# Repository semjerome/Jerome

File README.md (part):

---
csl: apa.csl
bibliography: GNoiseCitations.bib
title: Telematics
author: "Jerome Aganon, Jabneel Cruz, Jaewoong Kang, Achille Mattapullut"
---

\vfill   March 28th, 2017

\linespread{2} \selectfont

Project Build Website: http://Semjerome.github.io

Project Official website: http://www.autaccreport.com/wordpresstest/

\pagebreak

Declaration of Joint Authorship
===============================

We, the Galaxy Noise, confirm that this work submitted for assessment is our own
and is expressed in our own words. Any uses that was used in this documents that
came from any other authors were acknowledged where their works were used. A
list of references are included in this document and the work breakdown can be
find on Overall Description Section 2.3.

Galaxy Noise: Jerome Aganon, Jabneel Cruz, Jaewhoong Kang, Achille Mattapullut

Date: February 6, 2017

\pagebreak

Proposal
========

Submission January 17, 2017

Prepared by Galaxy Noise (Jerome, Jabneel, Jaewoong)

Computer Engineering Technology Student

https://semjerome.github.io

**Executive Summary**

As students in the Computer Engineering Technology program, we will be
integrating the knowledge and skills we have learned from our program into this
Internet of Things themed capstone project. This proposal requests the approval
to build the hardware portion that will connect to a database as well as to a
mobile device application. The internet connected hardware will include a custom
PCB with sensors and /or actuators for detecting car collision and save the
captured image/video in a black box The database will store the timestamp and
the folder location of the video that were saved in the blackbox. The mobile
device functionality will include notifying the car owner of an accident
happening and if possible, an image or video capture of the accident and will be
further detailed in the mobile application proposal. We will be collaborating
with the following company/department Engineering Club. The hardware will be
completed in CENG 317 Hardware Production Techniques independently and the
application will be completed in CENG 319 Software Project. These will be
integrated together in the subsequent term in CENG 355 Computer Systems Project
as a member of a 2 or 3 student group.

**Background**

The problem solved by project is to not to prevent any accident but to get
evidence if an accident happened. Having a dash cam does not mean that if an
accident happened there would be footage of what happened. Sometimes, accident
happens on the side or back of the car. In the event that such thing happened,
the people will rely on the story of a witness or the victims. Sometimes the
people will try to change their story in order for them to get away with it. If
such thing happens, the police will have to look around and see if a CCTV has
captured the accident.

I have searched for prior art via Humber’s IEEE subscription selecting “My
Subscribed Content” and have found and read which provides insight into similar
efforts.

The first journal that we found presents “ the approach to use smartphones as a
multi sensor platform in a field operational test respectively a naturalistic
driving study”. [@6758745]

The second journal talks about optical camera used for vehicles. [@7801077]

For the last journal, it then talks about inevitable accidents that can happen
with motorcycles and automobiles. [@7410053]

In the Computer Engineering Technology program we have learned about the
following topics from the respective relevant courses:

-   Java Docs from CENG 212 Programming Techniques In Java

-   Construction of circuits from CENG 215 Digital And Interfacing Systems,

-   Rapid application development and Gantt charts from CENG 216 Intro to
    Software Engineering,

-   Micro computing from CENG 252 Embedded Systems,

-   SQL from CENG 254 Database With Java,

-   Web access of databases from CENG 256 Internet Scripting; and,

-   Wireless protocols such as 802.11 from TECH152 Telecom Networks.

This knowledge and skill set will enable me to build the subsystems and
integrate them together as my capstone project. \pagebreak

**Methodology**

This proposal is assigned in the first week of class and is due at the beginning
of class in the second week of the fall semester. My coursework will focus on
the first two of the 3 phases of this project: Phase 1 Hardware build. Phase 2
System integration. Phase 3 Demonstration to future employers.

Phase 1 Hardware build

The hardware build will be completed in the fall term. It will fit within the
CENG Project maximum dimensions of 12 13/16" x 6" x 2 7/8" (32.5cm x 15.25cm x
7.25cm) which represents the space below the tray in the parts kit. The highest
AC voltage that will be used is 16Vrms from a wall adaptor from which +/- 15V or
as high as 45 VDC can be obtained. Maximum power consumption will be 20 Watts.

Phase 2 System integration

The system integration will be completed in the fall term.

Phase 3 Demonstration to future employers

This project will showcase the knowledge and skills that I have learned to
potential employers.

The tables below provide rough effort and non-labour estimates respectively for
each phase. A Gantt chart will be added by week 3 to provide more project
schedule details and a more complete budget will be added by week 4. It is
important to start tasks as soon as possible to be able to meet deadlines.

| **Labour Estimates**                                                                      | **Hrs**        | **Notes**                                                                                                                                              |
|-------------------------------------------------------------------------------------------|----------------|--------------------------------------------------------------------------------------------------------------------------------------------------------|
| **Phase 1**                                                                               |                |                                                                                                                                                        |
| Writing proposal.                                                                         | 9              | Tech identification quiz.                                                                                                                              |
| Creating project schedule. Initial project team meeting.                                  | 9              | Proposal due.                                                                                                                                          |
| Creating budget. Status Meeting.                                                          | 9              | Project Schedule due.                                                                                                                                  |
| Acquiring components and writing progress report.                                         | 9              | Budget due.                                                                                                                                            |
| Mechanical assembly and writing progress report. Status Meeting.                          | 9              | Progress Report due (components acquired milestone).                                                                                                   |
| PCB fabrication.                                                                          | 9              | Progress Report due (Mechanical Assembly milestone).                                                                                                   |
| Interface wiring, Placard design, Status Meeting.                                         | 9              | PCB Due (power up milestone).                                                                                                                          |
| Preparing for demonstration.                                                              | 9              | Placard due.                                                                                                                                           |
| Writing progress report and demonstrating project.                                        | 9              | Progress Report due (Demonstrations at Open House Saturday, November 12th, 2016 from 10 a.m. - 2 p.m.).                                                |
| Editing build video.                                                                      | 9              | Peer grading of demonstrations due.                                                                                                                    |
| Incorporation of feedback from demonstration and writing progress report. Status Meeting. | 9              | 30 second build video due.                                                                                                                             |
| Practice presentations                                                                    | 9              | Progress Report due.                                                                                                                                   |
| 1st round of Presentations, Collaborators present.                                        | 9              | Presentation PowerPoint file due.                                                                                                                      |
| 2nd round of Presentations                                                                | 9              | Build instructions up due.                                                                                                                             |
| Project videos, Status Meeting.                                                           | 9              | 30 second script due.                                                                                                                                  |
| **Phase 1 Total**                                                                         | **135**        |                                                                                                                                                        |
| **Phase 2**                                                                               |                |                                                                                                                                                        |
| Meet with collaborators                                                                   | 9              | Status Meeting                                                                                                                                         |
| Initial integration.                                                                      | 9              | Progress Report                                                                                                                                        |
| Meet with collaborators                                                                   | 9              | Status Meeting                                                                                                                                         |
| Testing.                                                                                  | 9              | Progress Report                                                                                                                                        |
| Meet with collaborators                                                                   | 9              | Status Meeting                                                                                                                                         |
| Meet with collaborators                                                                   | 9              | Status Meeting                                                                                                                                         |
| Incorporation of feedback.                                                                | 9              | Progress Report                                                                                                                                        |
| Meet with collaborators                                                                   | 9              | Status Meeting                                                                                                                                         |
| Testing.                                                                                  | 9              | Progress Report                                                                                                                                        |
| Meet with collaborators                                                                   | 9              | Status Meeting                                                                                                                                         |
| Prepare for demonstration.                                                                | 9              | Progress Report                                                                                                                                        |
| Complete presentation.                                                                    | 9              | Demonstration at Open House Saturday, April 8th, 2017 10 a.m. to 2 p.m.                                                                                |
| Complete final report. 1st round of Presentations.                                        | 9              | Presentation PowerPoint file due.                                                                                                                      |
| Write video script. 2nd round of Presentations, delivery of project.                      | 9              | Final written report including final budget and record of expenditures, covering both this semester and the previous semester.                         |
| Project videos.                                                                           | 9              | Video script due                                                                                                                                       |
| **Phase 2 Total**                                                                         | **135**        |                                                                                                                                                        |
| **Phase 3**                                                                               |                |                                                                                                                                                        |
| Interviews                                                                                | TBD            |                                                                                                                                                        |
| **Phase 3 Total**                                                                         | **TBD**        |                                                                                                                                                        |
| **Material Estimates**                                                                    | **Cost**       | **Notes**                                                                                                                                              |
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
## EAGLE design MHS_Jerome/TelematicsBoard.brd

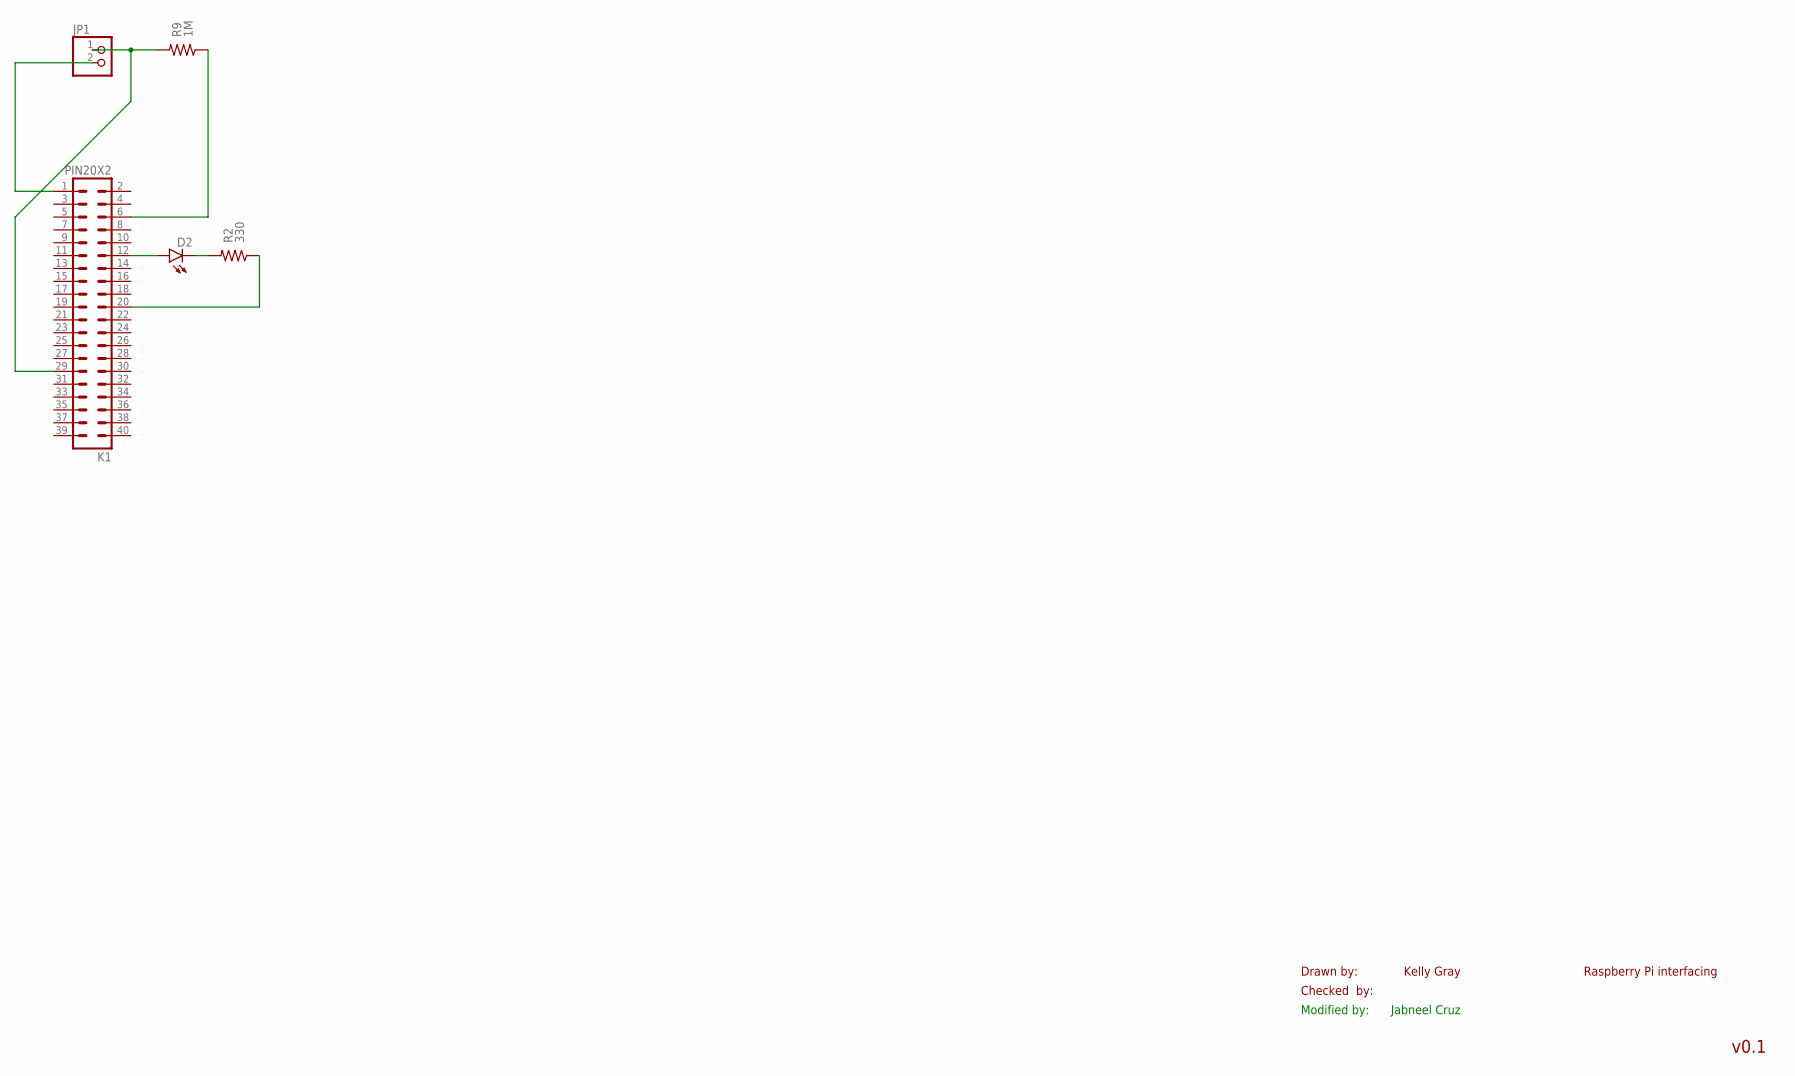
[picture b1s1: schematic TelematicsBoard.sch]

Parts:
D2: LED-3MM-NO_SILK; LED3MM-NS
JP1: PINHD-1X2; 1X02
K1: PIN20X2; PIN_20X2
R2: 330; AXIAL-0.3; TOLERANCE 5%
R9: 1M; AXIAL-0.3; TOLERANCE 5%

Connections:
unnamed: D2.A, K1.12
unnamed: JP1.2, K1.1
unnamed: D2.K (C), R2.P$2 (2)
unnamed: K1.20, R2.P$1 (1)
unnamed: K1.6, R9.P$1 (1)
unnamed: JP1.1, K1.29, R9.P$2 (2)

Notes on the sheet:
Drawn by:
Checked by:
Kelly Gray
v0.1
Raspberry Pi interfacing
Modified by:
Jabneel Cruz

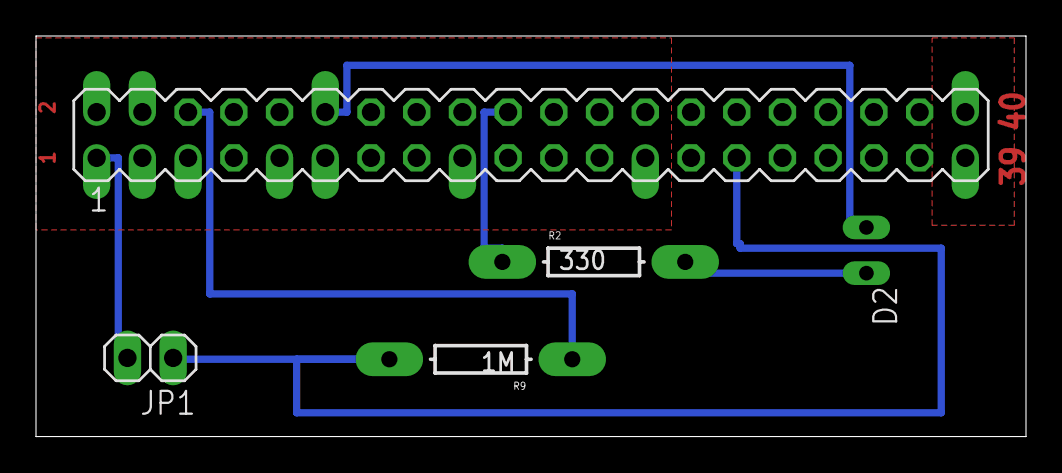
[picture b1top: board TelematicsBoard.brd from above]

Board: 2 copper layers, 55.0 x 22.3 mm, 5 parts (0 on the bottom side), 6 nets.

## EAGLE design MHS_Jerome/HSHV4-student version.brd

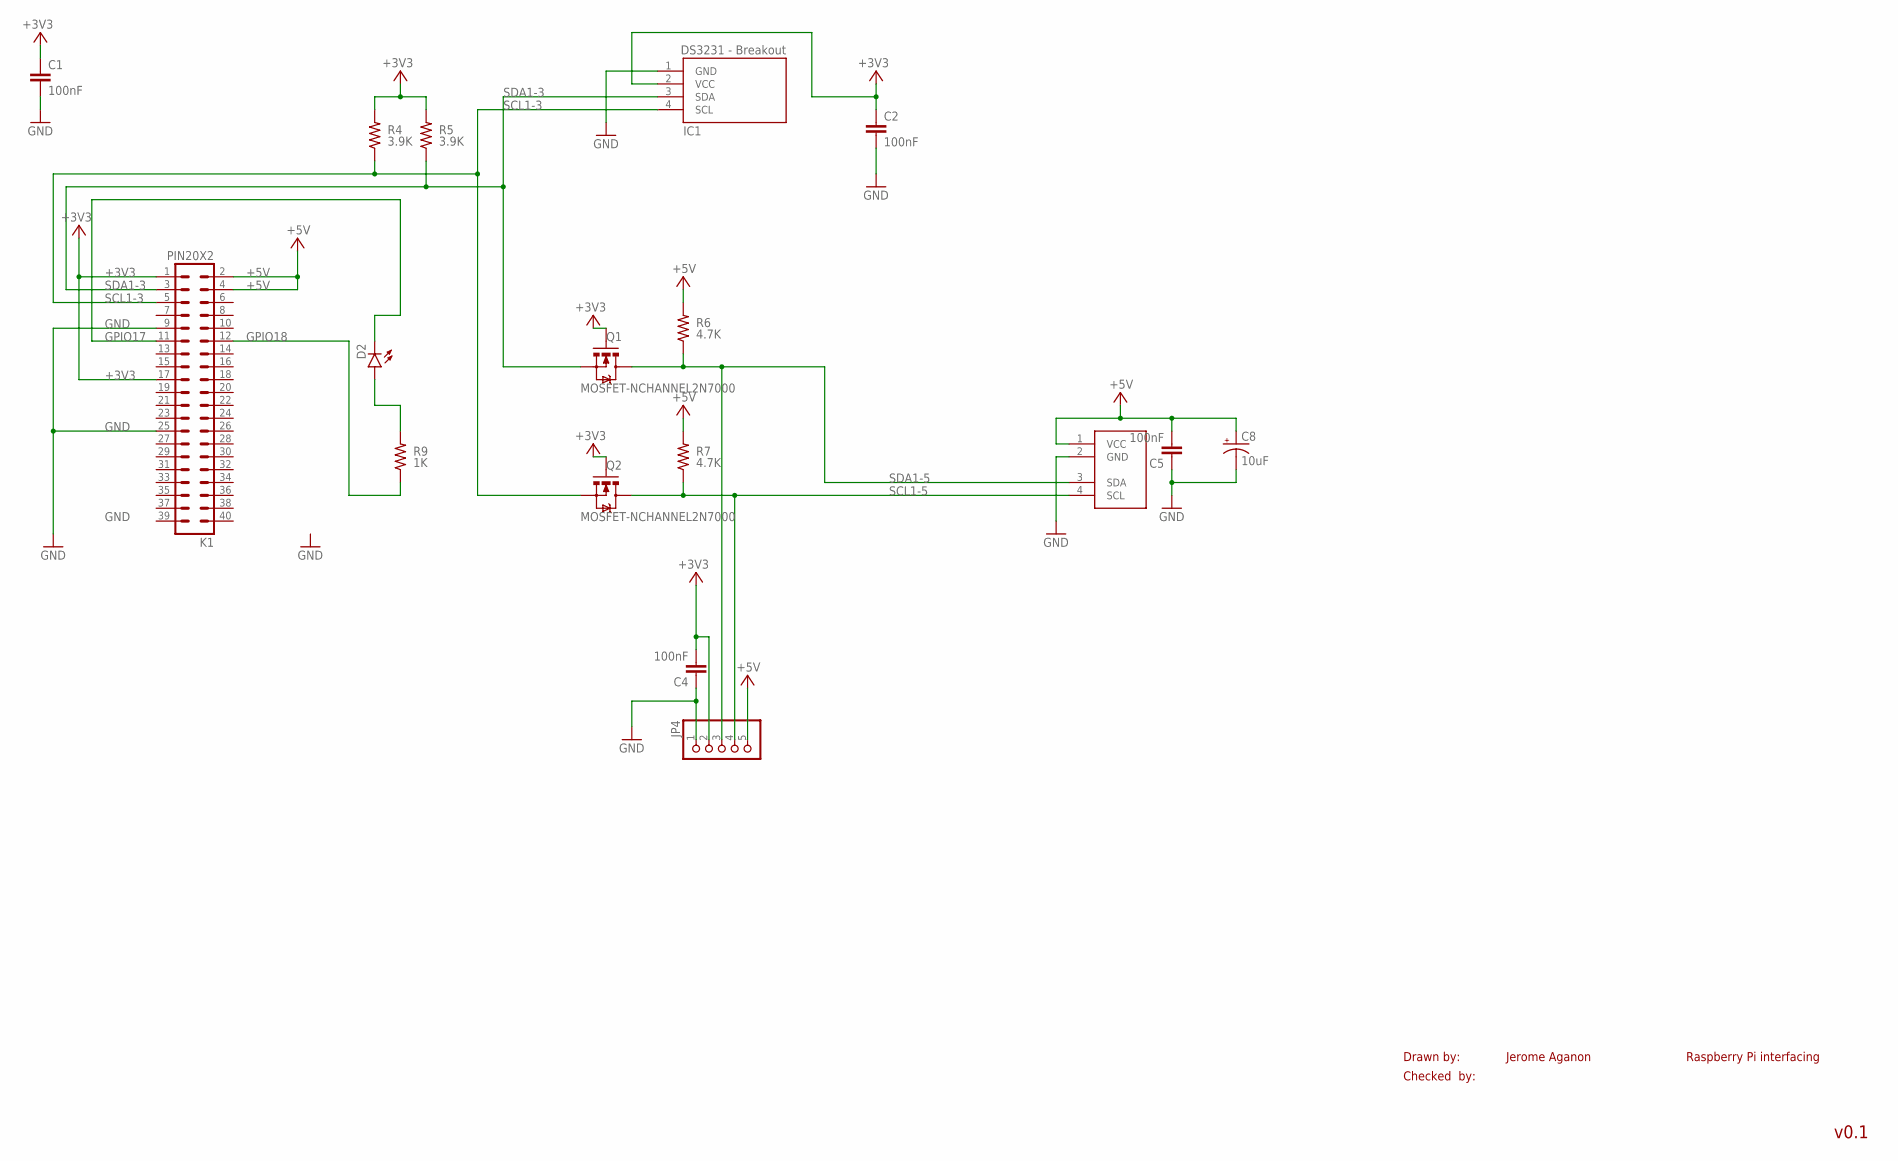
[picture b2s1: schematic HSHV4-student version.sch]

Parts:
C1, C2, C4, C5: 100nF; CAP-PTH-SMALL-KIT
C8: 10uF; CPOL-RADIAL-10UF-25V
D2: LED-3MM-NO_SILK; LED3MM-NS
IC1: DS3231; 8PTH
JP4: PINHD-1X5; 1X05
K1: PIN20X2; PIN_20X2
Q1, Q2: MOSFET-NCHANNEL2N7000; TO-92
R4, R5: 3.9K; AXIAL-0.3; TOLERANCE 5%
R6, R7: 4.7K; AXIAL-0.3; TOLERANCE 5%
R9: 1K; AXIAL-0.3; TOLERANCE 5%
U$1: PCF8591; 1X04

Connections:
+3V3: C1.1, C2.1, C4.2, IC1.2 (VCC), JP4.2, K1.1, K1.17, Q1.2 (G), Q2.2 (G), R4.P$2 (2), R5.P$2 (2)
+5V: C5.2, C8.1 (+), JP4.5, K1.2, K1.4, R6.P$2 (2), R7.P$2 (2), U$1.1 (VCC)
GND: C1.2, C2.2, C4.1, C5.1, C8.2 (-), IC1.1 (GND), JP4.1, K1.9, K1.25, U$1.2 (GND)
GPIO17: D2.K (C), K1.11
GPIO18: K1.12, R9.P$1 (1)
unnamed: D2.A, R9.P$2 (2)
SCL1-3: IC1.4 (SCL), K1.5, Q2.1 (S), R4.P$1 (1)
SCL1-5: JP4.4, Q2.3 (D), R7.P$1 (1), U$1.4 (SCL)
SDA1-3: IC1.3 (SDA), K1.3, Q1.1 (S), R5.P$1 (1)
SDA1-5: JP4.3, Q1.3 (D), R6.P$1 (1), U$1.3 (SDA)

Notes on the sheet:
Drawn by:
Checked by:
Jerome Aganon
v0.1
Raspberry Pi interfacing

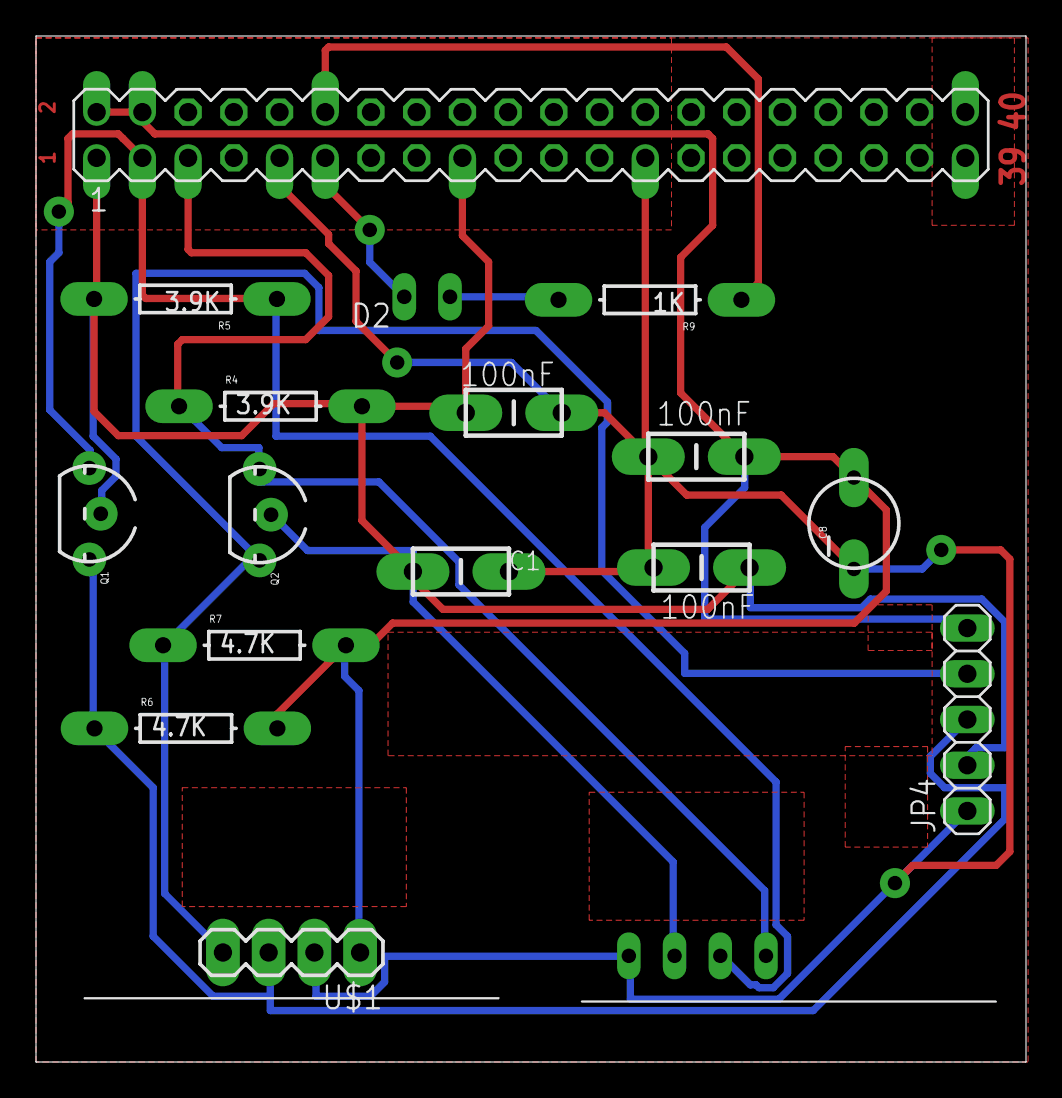
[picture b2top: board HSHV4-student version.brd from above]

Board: 2 copper layers, 55.0 x 57.0 mm, 17 parts (0 on the bottom side), 10 nets.

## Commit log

2016-09-20 Index
    Index.html has been added
2016-10-04 update index
2016-10-04 upload video
2017-03-21 reupload readme.md and readme.pdf
2017-03-28 Android Application Build
2017-03-28 fix android build formatting

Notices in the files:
README.md:
String  license = intent.getStringExtra("license");
String DRIVERLICENSE = null, FNAME=null,LNAME = null, GENDER = null, INSURANCENUMBER = null;
etLicense= (EditText) view.findViewById(R.id.etLicense);
DRIVERLICENSE = etLicense.getText().toString();
String driverlicense = params[0];
String urlParams = "driverlicense=" + driverlicense + "&fname=" + fname + "&lname="
String driverlicense = incidentJsonObject
\$driverlicense = \$\_POST["driverlicense"]; \$fname = \$\_POST["fname"];
